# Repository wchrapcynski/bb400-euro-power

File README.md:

# BB400 Eurorack Power Breakout

A minimal, U-shaped Eurorack power breakout PCB designed to plug directly into the power rails of a **BusBoard BB400** (400-tie-point) solderless breadboard without blocking the main prototyping area.

> **Status (`v0.1` - Ready for Prototype Fabrication):** Schematic and 2-layer PCB layout pass ERC and DRC with 0 errors and 0 warnings. Rail header spacing (`47.0 mm` outer-to-outer) has been caliper-verified against a physical BusBoard BB400. *(Hardware prototype test pending.)*

<!-- Optional: add your KiCad 3D render PNG here once exported

-->

## Features

- Connects to any standard **16-pin Eurorack power supply** (`+12V`, `-12V`, `+5V`, `GND`) via a keyed shrouded IDC header
- **U-shaped outline** (`55 x 32 mm`) sits cleanly off the end of the `54 mm` wide BB400 and leaves all 30 tie-point rows unobstructed
- **250 mA resettable PTC polyfuses** on all three voltage rails to protect your Eurorack case PSU from accidental breadboard shorts
- **Local rail filtering** (`10 uF` electrolytic + `100 nF` ceramic) on `+12V`, `+5V`, and `-12V`
- **2x2 underside male headers** (`47.0 mm` outer-to-outer) on each arm for a solid mechanical grip in the breadboard rails
- 100% through-hole (THT) components for easy hand-soldering

## Breadboard Rail Mapping

- **Left Arm (`J2`):** Outer rail (`+` red) = **`+12V`** | Inner rail (`-` black) = **`GND`**
- **Right Arm (`J3`):** Inner rail (`-` black) = **`-12V`** | Outer rail (`+` red) = **`+5V`**

## Bill of Materials (BOM) ([Interactive BOM](https://wchrapcynski.github.io/bb400-euro-power/bom/ibom.html))

| Ref | Qty | Value / Description | Footprint / Notes |
| :--- | :---: | :--- | :--- |
| `J1` | 1 | 2x8 (16-pin) Shrouded IDC Header, 2.54 mm | Vertical, keyed (Eurorack power) |
| `J2`, `J3` | 2 | 2x2 Male Pin Header, 2.54 mm | Mounted on **bottom** (`B.Cu`) |
| `F1`-`F3` | 3 | 250 mA Resettable PTC Polyfuse (30-60 V radial) | 5.1 mm pitch (e.g., Bourns `MF-R025` / Littelfuse `RXEF025`) |
| `C1`-`C3` | 3 | 10 uF, 25-35 V Electrolytic Capacitor | Radial, 5 mm dia, 2.0 mm pitch *(note reversed polarity on `C3` for `-12V`)* |
| `C4`-`C6` | 3 | 100 nF (0.1 uF), 50 V Ceramic Capacitor | Radial, 5.0 mm pitch |

## Assembly Notes

1. Solder all top-side components (`J1`, `F1`-`F3`, `C1`-`C6`) first. **Double-check `C3` polarity** - on the `-12V` rail, its `+` lead connects to `GND` and its `-` lead connects to `-12V`.
2. For effortless alignment, plug the `J2` and `J3` male pin headers into your BB400's power rails first, drop the PCB onto the pins, and solder them in place.
3. Verify `+12V`, `+5V`, and `-12V` with a multimeter before powering a circuit on the breadboard.

## Fabrication

- **Layers:** 2-layer FR4, 1.6 mm thickness, 1 oz copper
- **Designed in:** KiCad 10
- **OSH Park:** Upload the `.kicad_pcb` file directly.

## License

(c) 2026 William Chrapcynski - Licensed under **CC BY-NC-SA 4.0** (Attribution-NonCommercial-ShareAlike 4.0 International).

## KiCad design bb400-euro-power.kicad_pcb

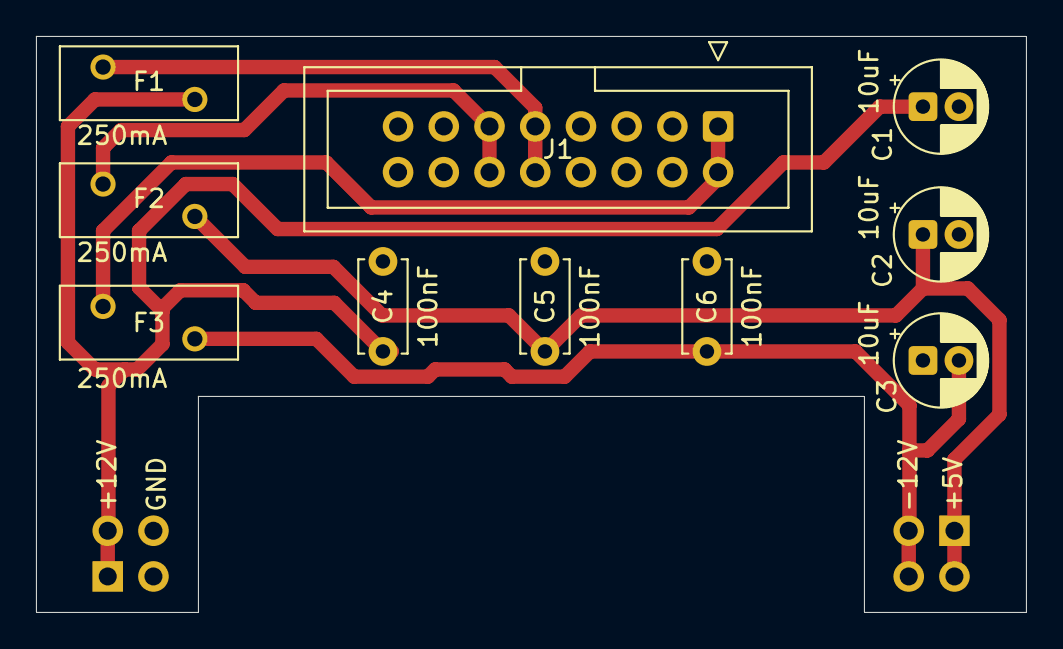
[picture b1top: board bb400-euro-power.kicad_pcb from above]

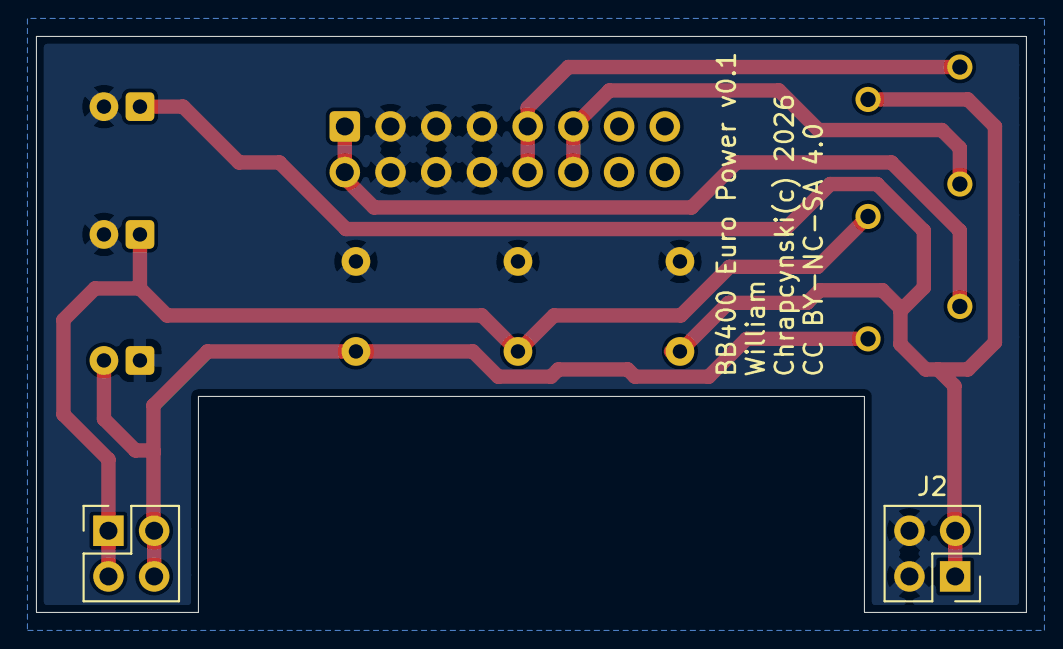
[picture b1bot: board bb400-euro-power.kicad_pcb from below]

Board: 2 copper layers, 55.0 x 32.0 mm, 12 parts (2 on the bottom side), 7 nets.

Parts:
C1, C2, C3: 10uF; CP_Radial_D5.0mm_P2.00mm
C4, C5, C6: 100nF; C_Disc_D5.0mm_W2.5mm_P5.00mm
F1, F2, F3: 250mA; Fuse_BelFuse_0ZRE0025FF_L9.6mm_W3.8mm
J1: Conn_02x08; IDC-Header_2x08_P2.54mm_Vertical
J2, J3: Conn_02x02; PinHeader_2x02_P2.54mm_Vertical

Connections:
+5V: C2.1, C5.1, F2.2, J3.1, J3.3
+12V: C1.1, C4.1, F1.2, J2.1, J2.3
-12V: C3.2, C6.1, F3.2, J3.2, J3.4
/+5V_IN: F2.1, J1.11, J1.12
/+12V_IN: F1.1, J1.9, J1.10
/-12V_IN: F3.1, J1.1, J1.2
GND: C1.2, C2.2, C3.1, C4.2, C5.2, C6.2, J1.3, J1.4, J1.5, J1.6, J1.7, J1.8, J2.2, J2.4

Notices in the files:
bb400-euro-power.kicad_pcb:
Chrapcynski(c) 2026
CC BY-NC-SA 4.0
